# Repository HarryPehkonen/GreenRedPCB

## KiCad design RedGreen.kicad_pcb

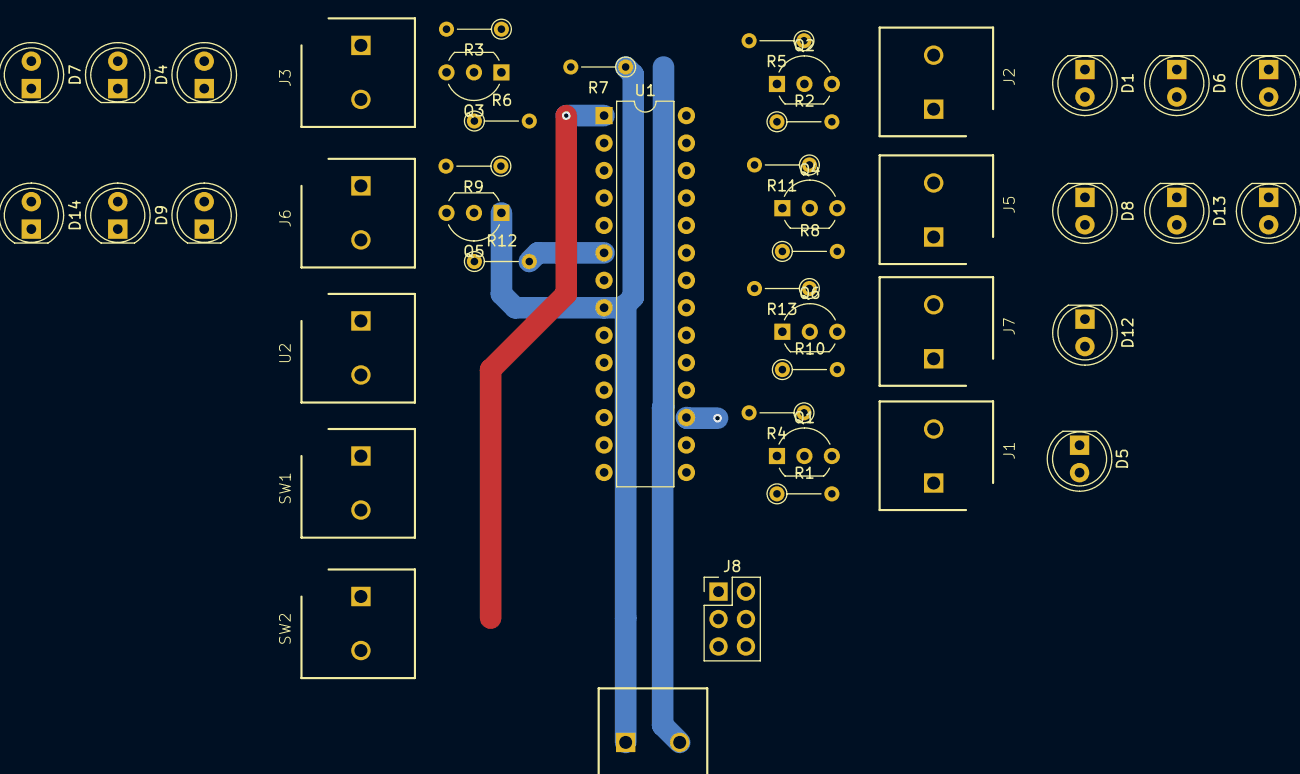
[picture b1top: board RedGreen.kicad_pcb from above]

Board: 2 copper layers, 46 parts (1 on the bottom side), 33 nets.

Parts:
C1: 100nF; C_1206_3216Metric
D1, D2, D3, D4, D5, D6, D7, D8, D9, D10, D11, D12, D13, D14: LED; LED_D5.0mm
J1, J2, J3, J5, J6, J7: ScrewTerm; ScrewTermGreenEbay
J4: Power; ScrewTermGreenEbay
J8: Conn_02x03_Odd_Even; PinHeader_2x03_P2.54mm_Vertical
Q1, Q2, Q3, Q4, Q5, Q6: PN2222A; TO-92_Inline_Wide
R1, R10: 200; R_Axial_DIN0204_L3.6mm_D1.6mm_P5.08mm_Vertical
R2, R3, R8, R9: 51; R_Axial_DIN0204_L3.6mm_D1.6mm_P5.08mm_Vertical
R4, R5, R6, R11, R12, R13: 4k; R_Axial_DIN0204_L3.6mm_D1.6mm_P5.08mm_Vertical
R7: 10k; R_Axial_DIN0204_L3.6mm_D1.6mm_P5.08mm_Vertical
SW1: SW_Push; ScrewTermGreenEbay
SW2: SW_Reed; ScrewTermGreenEbay
U1: ATmega328P-PU; DIP-28_W7.62mm
U2: IR; ScrewTermGreenEbay

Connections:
BTN: SW1.1, U1.12
GND: C1.2, J4.1, J8.6, Q1.1, Q2.1, Q3.1, Q4.1, Q5.1, Q6.1, R7.1, SW1.2, SW2.2, U1.8, U1.22, U2.2
GREEN1: R11.2, U1.5
GREEN2: R12.2, U1.6
GREEN_BACK: R13.2, U1.11
ICP1: U1.14, U2.1
MISO: J8.1, U1.18
MOSI: J8.4, U1.17
unnamed: D1.1, D3.1, D6.1, J2.2, Q2.3
unnamed: D1.2, D3.2, D6.2, J2.1, R2.2
unnamed: D2.1, D4.1, D7.1, J3.2, Q3.3
unnamed: D2.2, D4.2, D7.2, J3.1, R3.2
unnamed: D5.1, J1.2, Q1.3
unnamed: D5.2, J1.1, R1.2
unnamed: D8.1, D10.1, D13.1, J5.2, Q4.3
unnamed: D8.2, D10.2, D13.2, J5.1, R8.2
unnamed: D9.1, D11.1, D14.1, J6.2, Q5.3
unnamed: D9.2, D11.2, D14.2, J6.1, R9.2
unnamed: D12.1, J7.2, Q6.3
unnamed: D12.2, J7.1, R10.2
unnamed: Q1.2, R4.1
unnamed: Q2.2, R5.1
unnamed: Q3.2, R6.1
unnamed: Q4.2, R11.1
unnamed: Q5.2, R12.1
unnamed: Q6.2, R13.1
RED1: R5.2, U1.2
RED2: R6.2, U1.3
RED_BACK: R4.2, U1.4
REED: SW2.1, U1.13
RST: C1.1, J8.5, R7.2, U1.1
SCK: J8.3, U1.19
VCC: J4.2, J8.2, R1.1, R2.1, R3.1, R8.1, R9.1, R10.1, U1.7

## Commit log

2021-02-16 start
2021-02-19 not sure
2021-02-19 changed IR power to switchable
